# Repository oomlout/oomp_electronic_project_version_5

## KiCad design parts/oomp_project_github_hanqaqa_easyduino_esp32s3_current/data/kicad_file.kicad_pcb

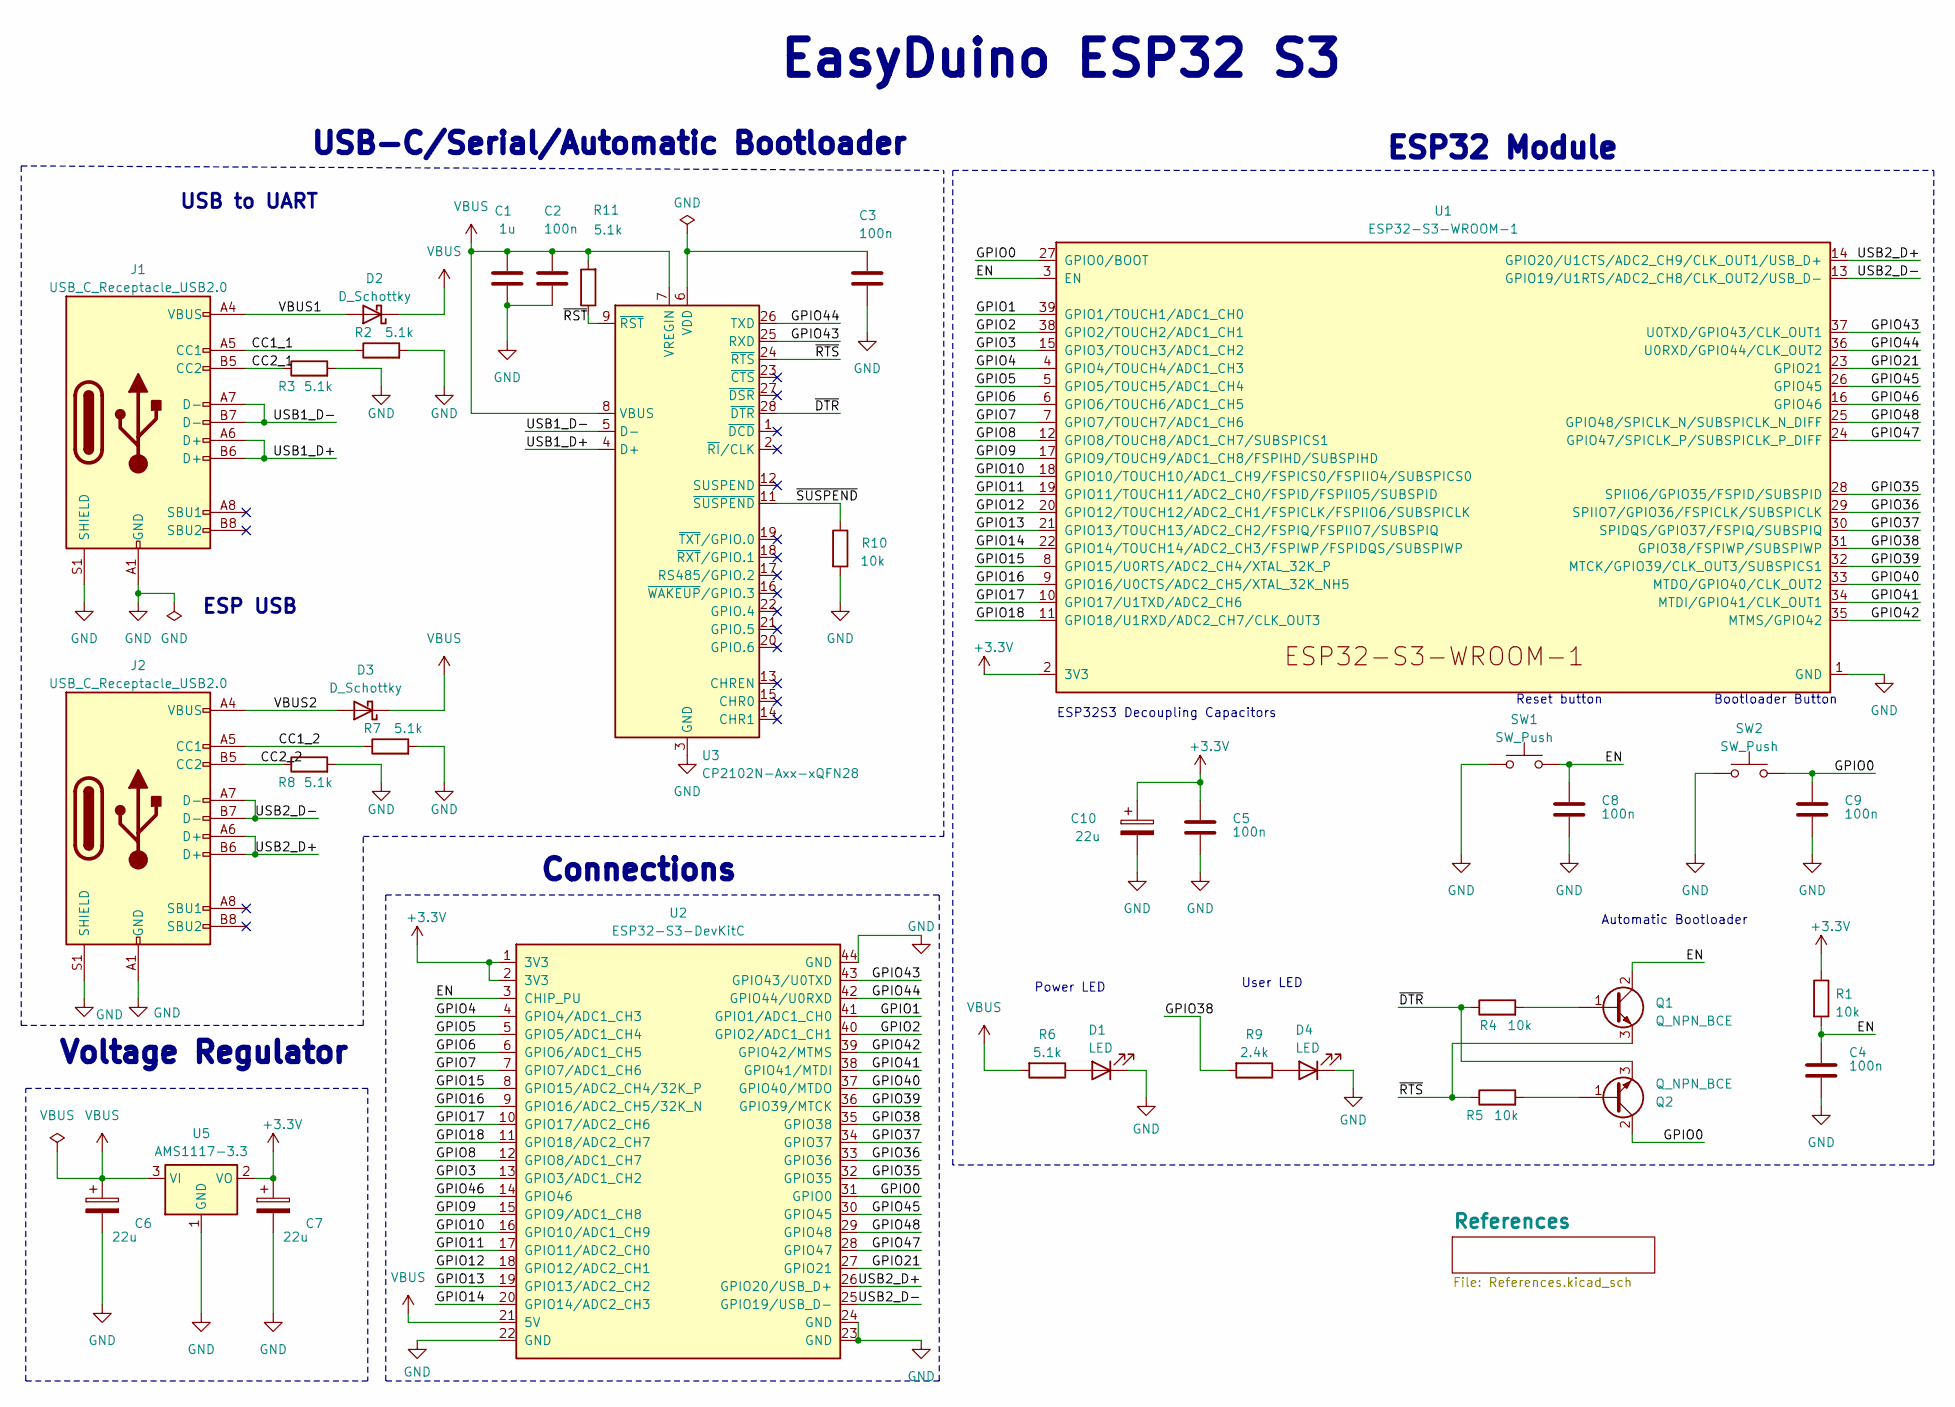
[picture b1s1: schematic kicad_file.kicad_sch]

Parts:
C1: 1u; C_0402_1005Metric; LCSC C52923
C2, C3, C4, C5, C8, C9: 100n; C_0402_1005Metric; LCSC C1525
C6, C7, C10: 22u; CP_EIA-3216-10_Kemet-I; LCSC C11366
D1, D4: LED; LED_0402_1005Metric; LCSC C434447
D2, D3: D_Schottky; D_0402_1005Metric; LCSC C2837790
J1, J2: USB_C_Receptacle_USB2.0; USB_C_Receptacle_G-Switch_GT-USB-7010ASV; LCSC C2765186
Q1, Q2: Q_NPN_BCE; SOT-23W; LCSC C916392
R1, R4, R5, R10: 10k; R_0402_1005Metric; LCSC C25744
R2, R3, R6, R7, R8, R11: 5.1k; R_0402_1005Metric; LCSC C25905
R9: 2.4k; R_0402_1005Metric; LCSC C25882
SW1, SW2: SW_Push; SW_Push_SPST_NO_Alps_SKRK; LCSC C720477
U1: ESP32-S3-WROOM-1; LCSC C2913197
U2: ESP32-S3-DevKitC
U3: CP2102N-Axx-xQFN28; QFN-28-1EP_5x5mm_P0.5mm_EP3.35x3.35mm; LCSC C6568
U5: AMS1117-3.3; SOT-223-3_TabPin2; LCSC C6186

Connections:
+3.3V: C5.1, C7.1, C10.1, R1.1, U1.2 (3V3), U2.1 (3V3), U2.2 (3V3), U5.2 (VO)
/CC1_1: J1.A5 (CC1), R2.1
/CC1_2: J2.A5 (CC1), R7.1
/CC2_1: J1.B5 (CC2), R3.1
/CC2_2: J2.B5 (CC2), R8.1
/EN: C4.1, C8.1, Q1.2 (C), R1.2, SW1.2, U1.3 (EN), U2.3 (CHIP_PU)
/GPIO0: C9.1, Q2.2 (C), SW2.2, U1.27 (GPIO0/BOOT), U2.31 (GPIO0)
/GPIO1: U1.39 (GPIO1/TOUCH1/ADC1_CH0), U2.41 (GPIO1/ADC1_CH0)
/GPIO2: U1.38 (GPIO2/TOUCH2/ADC1_CH1), U2.40 (GPIO2/ADC1_CH1)
/GPIO3: U1.15 (GPIO3/TOUCH3/ADC1_CH2), U2.13 (GPIO3/ADC1_CH2)
/GPIO4: U1.4 (GPIO4/TOUCH4/ADC1_CH3), U2.4 (GPIO4/ADC1_CH3)
/GPIO5: U1.5 (GPIO5/TOUCH5/ADC1_CH4), U2.5 (GPIO5/ADC1_CH4)
/GPIO6: U1.6 (GPIO6/TOUCH6/ADC1_CH5), U2.6 (GPIO6/ADC1_CH5)
/GPIO7: U1.7 (GPIO7/TOUCH7/ADC1_CH6), U2.7 (GPIO7/ADC1_CH6)
/GPIO8: U1.12 (GPIO8/TOUCH8/ADC1_CH7/SUBSPICS1), U2.12 (GPIO8/ADC1_CH7)
/GPIO9: U1.17 (GPIO9/TOUCH9/ADC1_CH8/FSPIHD/SUBSPIHD), U2.15 (GPIO9/ADC1_CH8)
/GPIO10: U1.18 (GPIO10/TOUCH10/ADC1_CH9/FSPICS0/FSPIIO4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), U2.16 (GPIO10/ADC1_CH9)
/GPIO11: U1.19 (GPIO11/TOUCH11/ADC2_CH0/FSPID/FSPIIO5/S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), U2.17 (GPIO11/ADC2_CH0)
/GPIO12: U1.20 (GPIO12/TOUCH12/ADC2_CH1/FSPICLK/FSPIIO6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), U2.18 (GPIO12/ADC2_CH1)
/GPIO13: U1.21 (GPIO13/TOUCH13/ADC2_CH2/FSPIQ/FSPIIO7/S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), U2.19 (GPIO13/ADC2_CH2)
/GPIO14: U1.22 (GPIO14/TOUCH14/ADC2_CH3/FSPIWP/FSPIDQS/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), U2.20 (GPIO14/ADC2_CH3)
/GPIO15: U1.8 (GPIO15/U0RTS/ADC2_CH4/XTAL_32K_P), U2.8 (GPIO15/ADC2_CH4/32K_P)
/GPIO16: U1.9 (GPIO16/U0CTS/ADC2_CH5/XTAL_32K_NH5), U2.9 (GPIO16/ADC2_CH5/32K_N)
/GPIO17: U1.10 (GPIO17/U1TXD/ADC2_CH6), U2.10 (GPIO17/ADC2_CH6)
/GPIO18: U1.11 (GPIO18/U1RXD/ADC2_CH7/CLK_OUT3), U2.11 (GPIO18/ADC2_CH7)
/GPIO21: U1.23 (GPIO21), U2.27 (GPIO21)
/GPIO35: U1.28 (SPIIO6/GPIO35/FSPID/SUBSPID), U2.32 (GPIO35)
/GPIO36: U1.29 (SPIIO7/GPIO36/FSPICLK/SUBSPICLK), U2.33 (GPIO36)
/GPIO37: U1.30 (SPIDQS/GPIO37/FSPIQ/SUBSPIQ), U2.34 (GPIO37)
/GPIO38: R9.2, U1.31 (GPIO38/FSPIWP/SUBSPIWP), U2.35 (GPIO38)
/GPIO39: U1.32 (MTCK/GPIO39/CLK_OUT3/SUBSPICS1), U2.36 (GPIO39/MTCK)
/GPIO40: U1.33 (MTDO/GPIO40/CLK_OUT2), U2.37 (GPIO40/MTDO)
/GPIO41: U1.34 (MTDI/GPIO41/CLK_OUT1), U2.38 (GPIO41/MTDI)
/GPIO42: U1.35 (MTMS/GPIO42), U2.39 (GPIO42/MTMS)
/GPIO43: U1.37 (U0TXD/GPIO43/CLK_OUT1), U2.43 (GPIO43/U0TXD), U3.25 (RXD)
/GPIO44: U1.36 (U0RXD/GPIO44/CLK_OUT2), U2.42 (GPIO44/U0RXD), U3.26 (TXD)
/GPIO45: U1.26 (GPIO45), U2.30 (GPIO45)
/GPIO46: U1.16 (GPIO46), U2.14 (GPIO46)
/GPIO47: U1.24 (GPIO47/SPICLK_P/SUBSPICLK_P_DIFF), U2.28 (GPIO47)
/GPIO48: U1.25 (GPIO48/SPICLK_N/SUBSPICLK_N_DIFF), U2.29 (GPIO48)
/USB1_D+: J1.A6 (D+), J1.B6 (D+), U3.4 (D+)
/USB1_D-: J1.A7 (D-), J1.B7 (D-), U3.5 (D-)
/USB2_D+: J2.A6 (D+), J2.B6 (D+), U1.14 (GPIO20/U1CTS/ADC2_CH9/CLK_OUT1/USB_D+), U2.26 (GPIO20/USB_D+)
/USB2_D-: J2.A7 (D-), J2.B7 (D-), U1.13 (GPIO19/U1RTS/ADC2_CH8/CLK_OUT2/USB_D-), U2.25 (GPIO19/USB_D-)
/VBUS1: D2.2 (A), J1.A4 (VBUS), J1.A9 (VBUS), J1.B4 (VBUS), J1.B9 (VBUS)
/VBUS2: D3.2 (A), J2.A4 (VBUS), J2.A9 (VBUS), J2.B4 (VBUS), J2.B9 (VBUS)
/~DTR: Q2.3 (E), R4.1, U3.28 (~DTR)
/~RST: R11.1, U3.9 (~RST)
/~RTS: Q1.3 (E), R5.1, U3.24 (~RTS)
/~SUSPEND: R10.1, U3.11 (~SUSPEND)
GND: C1.2, C2.2, C3.2, C4.2, C5.2, C6.2, C7.2, C8.2, C9.2, C10.2, D1.1 (K), D4.1 (K), J1.A1 (GND), J1.A12 (GND), J1.B1 (GND), J1.B12 (GND), J1.S1 (SHIELD), J2.A1 (GND), J2.A12 (GND), J2.B1 (GND), J2.B12 (GND), J2.S1 (SHIELD), R2.2, R3.2, R7.2, R8.2, R10.2, SW1.1, SW2.1, U1.1 (GND), U1.40 (GND), U1.41 (GND), U2.22 (GND), U2.23 (GND), U2.24 (GND), U2.44 (GND), U3.3 (GND), U3.29 (GND), U5.1 (GND)
unnamed: D1.2 (A), R6.1
unnamed: D4.2 (A), R9.1
unnamed: Q1.1 (B), R4.2
unnamed: Q2.1 (B), R5.2
unnamed: C3.1, U3.6 (VDD)
VBUS: C1.1, C2.1, C6.1, D2.1 (K), D3.1 (K), R6.2, R11.2, U2.21 (5V), U3.7 (VREGIN), U3.8 (VBUS), U5.3 (VI)

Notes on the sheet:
Automatic Bootloader
ESP USB
Power LED
ESP32 Module
User LED
USB-C/Serial/Automatic Bootloader
ESP32S3 Decoupling Capacitors
Connections
USB to UART
Voltage Regulator
Bootloader Button
EasyDuino ESP32 S3
Reset button

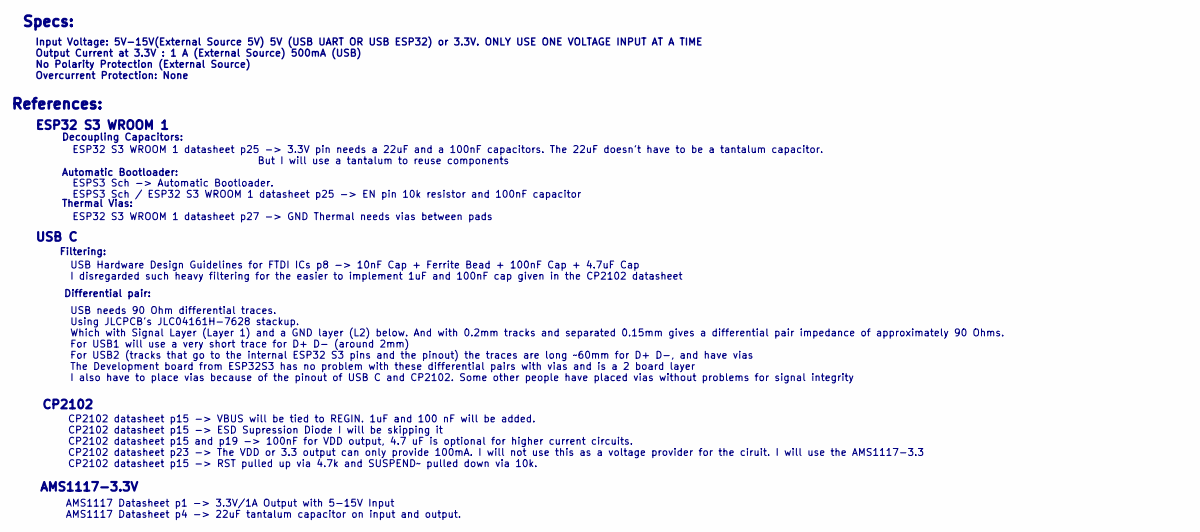
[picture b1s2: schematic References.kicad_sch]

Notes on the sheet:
Filtering:
Input Voltage: 5V-15V(External Source 5V) 5V (USB UART OR USB ESP32) or 3.3V. ONLY USE ONE VOLTAGE INPUT AT A TIME Output Current at 3.3V : 1 A (External Source) 500mA (USB) No Polarity Protection (External Source) Overcurrent Protection: None
Thermal Vias:
References:
ESP32 S3 WROOM 1
ESP32 S3 WROOM 1 datasheet p25 -> 3.3V pin needs a 22uF and a 100nF capacitors. The 22uF doesn't have to be a tantalum capacitor. But I will use a tantalum to reuse components ESPS3 Sch -> Automatic Bootloader. ESPS3 Sch / ESP32 S3 WROOM 1 datasheet p25 -> EN pin 10k resistor and 100nF capacitor ES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
Specs:
USB C
AMS1117-3.3V
CP2102 datasheet p15 -> VBUS will be tied to REGIN. 1uF and 100 nF will be added. CP2102 datasheet p15 -> ESD Supression Diode I will be skipping it CP2102 datasheet p15 and p19 -> 100nF for VDD output, 4.7 uF is optional for higher current circuits. CP2102 datasheet p23 -> The VDD or 3.3 output ca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
AMS1117 Datasheet p1 -> 3.3V/1A Output with 5-15V Input AMS1117 Datasheet p4 -> 22uF tantalum capacitor on input and output.
CP2102
Decoupling Capacitors:
USB needs 90 Ohm differential traces. Using JLCPCB's JLC04161H-7628 stackup. Which with Signal Layer (Layer 1) and a GND layer (L2) below. And with 0.2mm tracks and separated 0.15mm gives a differential pair impedance of approximately 90 Ohms. For USB1 will use a very short trace for D+ D- (around 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
Automatic Bootloader:
USB Hardware Design Guidelines for FTDI ICs p8 -> 10nF Cap + Ferrite Bead + 100nF Cap + 4.7uF Cap I disregarded such heavy filtering for the easier to implement 1uF and 100nF cap given in the CP2102 datasheet
Differential pair:

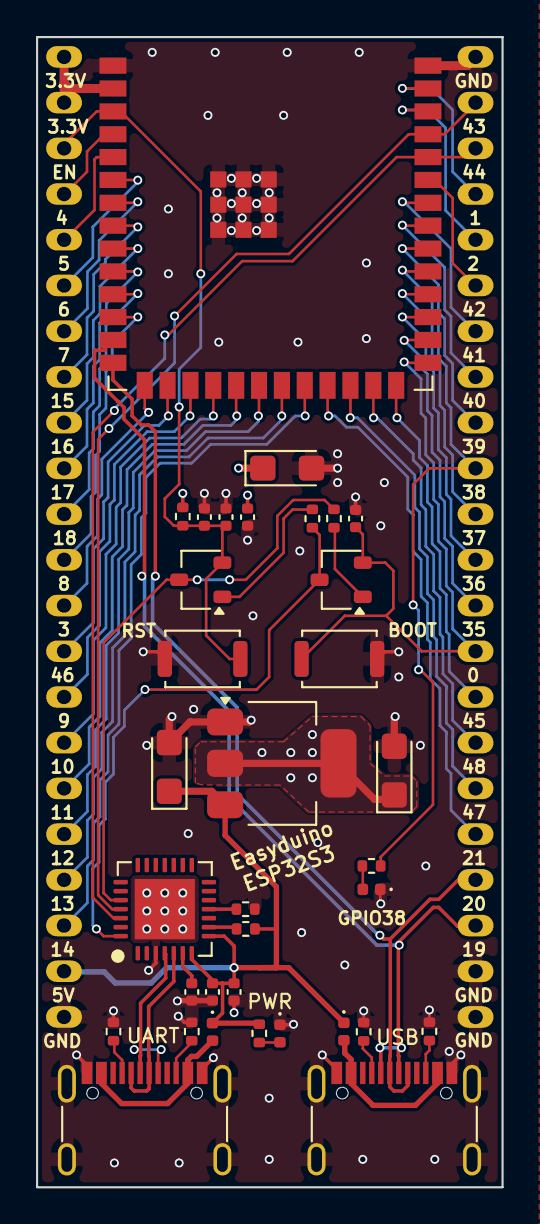
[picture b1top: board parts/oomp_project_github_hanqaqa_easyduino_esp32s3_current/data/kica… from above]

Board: 4 copper layers, 25.9 x 63.9 mm, 35 parts (0 on the bottom side), 57 nets.

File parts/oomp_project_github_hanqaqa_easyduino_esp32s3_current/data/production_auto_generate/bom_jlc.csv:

Comment,Designator,Footprint,LCSC Part #
100n,"C2,C3,C4,C5,C8,C9",Capacitor_SMD:C_0402_1005Metric,C1525
10k,"R1,R4,R5,R10",Resistor_SMD:R_0402_1005Metric,C25744
1u,C1,Capacitor_SMD:C_0402_1005Metric,C52923
2.4k,R9,Resistor_SMD:R_0402_1005Metric,C25882
22u,"C6,C7,C10",Capacitor_Tantalum_SMD:CP_EIA-3216-10_Kemet-I,C11366
5.1k,"R2,R3,R6,R7,R8,R11",Resistor_SMD:R_0402_1005Metric,C25905
AMS1117-3.3,U5,Package_TO_SOT_SMD:SOT-223-3_TabPin2,C6186
CP2102N-Axx-xQFN28,U3,Package_DFN_QFN:QFN-28-1EP_5x5mm_P0.5mm_EP3.35x3.35mm,C6568
D_Schottky,"D2,D3",Diode_SMD:D_0402_1005Metric,C2837790
ESP32-S3-DevKitC,U2,Espressif:ESP32-S3-DevKitC,-
ESP32-S3-WROOM-1,U1,Espressif:ESP32-S3-WROOM-1,C2913197
LED,"D1,D4",LED_SMD:LED_0402_1005Metric,C434447
Q_NPN_BCE,"Q1,Q2",Package_TO_SOT_SMD:SOT-23W,C916392
SW_Push,"SW1,SW2",Button_Switch_SMD:SW_Push_SPST_NO_Alps_SKRK,C720477
USB_C_Receptacle_USB2.0,"J1,J2",Connector_USB:USB_C_Receptacle_G-Switch_GT-USB-7010ASV,C2765186

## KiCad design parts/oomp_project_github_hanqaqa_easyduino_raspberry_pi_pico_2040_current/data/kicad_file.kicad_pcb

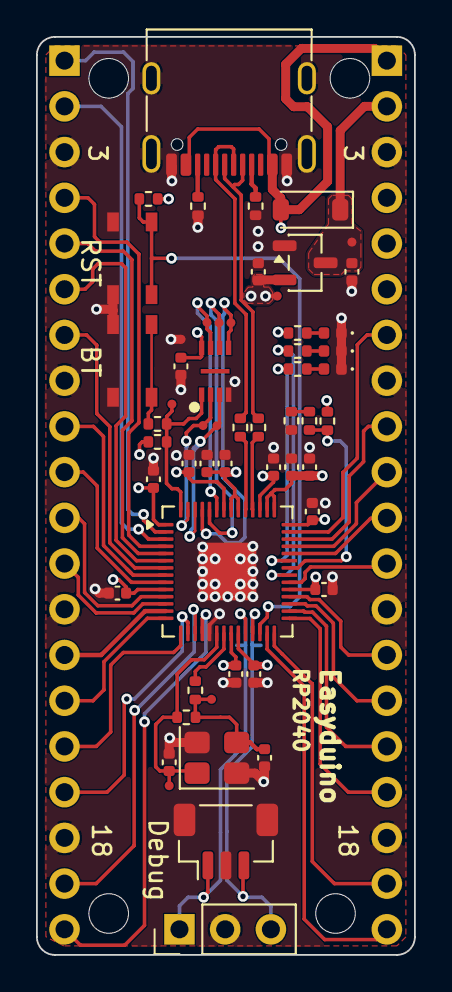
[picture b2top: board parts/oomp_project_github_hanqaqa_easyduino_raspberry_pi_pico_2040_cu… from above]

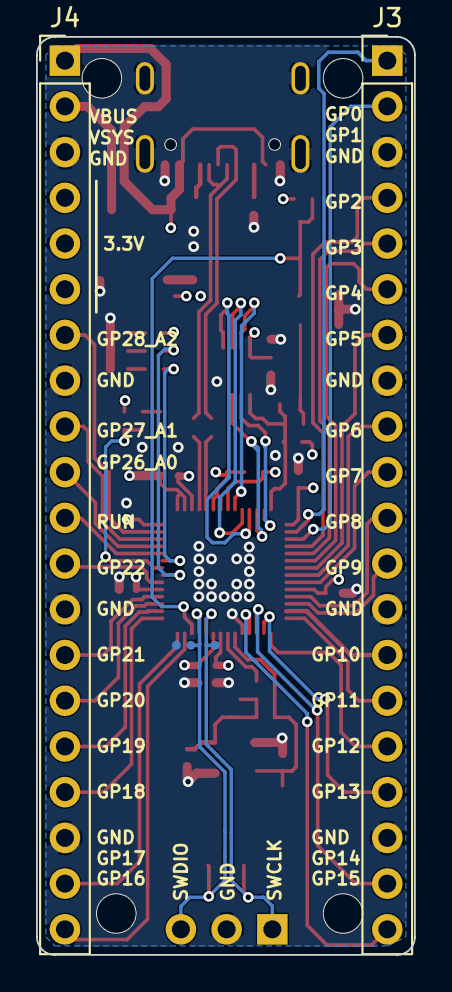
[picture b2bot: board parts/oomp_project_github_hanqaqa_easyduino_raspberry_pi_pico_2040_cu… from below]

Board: 4 copper layers, 21.0 x 51.0 mm, 65 parts (5 on the bottom side), 58 nets.

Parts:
C1, C2, C5, C6, C7, C8, C9, C10, C11, C12, C15: 100nF; C_0402_1005Metric
C3, C4, C13, C14: 1uF; C_0402_1005Metric
C16, C17: 27p; C_0402_1005Metric
D1: D_Schottky; D_SOD-123
D2, D3, D4: LED; LED_0402_1005Metric
H1, H2, H3, H4: MountingHole; MountingHole_2.2mm_M2
J1: USB_C_Receptacle_USB2.0; USB_C_Receptacle_G-Switch_GT-USB-7010ASV
J3, J4: Conn_01x20; PinHeader_1x20_P2.54mm_Vertical
J5: Conn_01x03; PinHeader_1x03_P2.54mm_Vertical
J6: Conn_01x03_MountingPin; JST_SH_BM03B-SRSS-TB_1x03-1MP_P1.00mm_Vertical
R1, R2, R3, R6, R7: 5.1k; R_0402_1005Metric
R4, R5: 27R; R_0402_1005Metric
R8, R9, R10, R11, R12, R13, R14, R15: 1k; R_0402_1005Metric
SW1, SW2: SW_Push; ALPSALPINE_SKRPACE010
TP1, TP2, TP3, TP4, TP5, TP6, TP7, TP8, TP9, TP10, TP11, TP12, TP13, TP14: TestPoint_pad
U1: XC6206P332MR; SOT-23-3
U2: RP2040; QFN-56-1EP_7x7mm_P0.4mm_EP3.2x3.2mm
U3: W25Q16JVUXIQ
Y1: 12MHz; Crystal_SMD_3225-4Pin_3.2x2.5mm

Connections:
+1V1: C1.1, C2.1, C3.1, U2.23 (DVDD), U2.45 (VREG_VOUT), U2.50 (DVDD)
+3.3V: C4.1, C5.1, C6.1, C7.1, C8.1, C9.1, C10.1, C11.1, C12.1, C14.1, C15.1, J4.4, J4.5, J4.6, R10.1, R11.1, R12.1, TP2.1 (1_1), U1.2 (VO), U2.1 (IOVDD), U2.10 (IOVDD), U2.22 (IOVDD), U2.33 (IOVDD), U2.42 (IOVDD), U2.43 (ADC_AVDD), U2.44 (VREG_IN), U2.48 (USB_VDD), U2.49 (IOVDD), U3.8 (VCC)
/CC1: J1.A5 (CC1), R1.1
/CC2: J1.B5 (CC2), R2.1
/GPIO0: J3.1, U2.2 (GPIO0)
/GPIO1: J3.2, U2.3 (GPIO1)
/GPIO2: J3.4, U2.4 (GPIO2)
/GPIO3: J3.5, U2.5 (GPIO3)
/GPIO4: J3.6, U2.6 (GPIO4)
/GPIO5: J3.7, U2.7 (GPIO5)
/GPIO6: J3.9, U2.8 (GPIO6)
/GPIO7: J3.10, U2.9 (GPIO7)
/GPIO8: J3.11, U2.11 (GPIO8)
/GPIO9: J3.12, U2.12 (GPIO9)
/GPIO10: J3.14, U2.13 (GPIO10)
/GPIO11: J3.15, U2.14 (GPIO11)
/GPIO12: J3.16, U2.15 (GPIO12)
/GPIO13: J3.17, U2.16 (GPIO13)
/GPIO14: J3.19, U2.17 (GPIO14)
/GPIO15: J3.20, U2.18 (GPIO15)
/GPIO16: J4.20, U2.27 (GPIO16)
/GPIO17: J4.19, U2.28 (GPIO17)
/GPIO18: J4.17, U2.29 (GPIO18)
/GPIO19: J4.16, U2.30 (GPIO19)
/GPIO20: J4.15, U2.31 (GPIO20)
/GPIO21: J4.14, U2.32 (GPIO21)
/GPIO22: J4.12, U2.34 (GPIO22)
/GPIO23: R13.1, U2.35 (GPIO23)
/GPIO24: R3.1, R6.2, U2.36 (GPIO24)
/GPIO25: R14.1, U2.37 (GPIO25)
/GPIO26_ADC0: J4.11, U2.38 (GPIO26_ADC0)
/GPIO27_ADC1: J4.10, U2.39 (GPIO27_ADC1)
/GPIO28_ADC2: J4.9, U2.40 (GPIO28_ADC2)
/GPIO29_ADC3: J4.7, U2.41 (GPIO29_ADC3)
/LED_3V3: D2.2 (A), R12.2
/LED_BUILT_IN1: D4.2 (A), R14.2
/LED_BUILT_IN2: D3.2 (A), R13.2
/QSPI_SCLK: TP9.1 (1_1), U2.52 (QSPI_SCLK), U3.6 (CLK)
/QSPI_SD0: TP10.1 (1_1), U2.53 (QSPI_SD0), U3.5 (DI(IO0))
/QSPI_SD1: TP11.1 (1_1), U2.55 (QSPI_SD1), U3.2 (DO(IO1))
/QSPI_SD2: TP12.1 (1_1), U2.54 (QSPI_SD2), U3.3 (IO2)
/QSPI_SD3: TP13.1 (1_1), U2.51 (QSPI_SD3), U3.7 (IO3)
/QSPI_SS: R10.2, R15.1, TP8.1 (1_1), U2.56 (QSPI_SS), U3.1 (~CS)
/RDIV: R6.1, R7.2
/RUN: R11.2, SW2.2, U2.26 (RUN)
/SW1_{PULL-UP}: R15.2, SW1.2
/SWCLK: J5.1, J6.1, TP5.1 (1_1), U2.24 (SWCLK)
/SWD: J5.3, J6.3, TP6.1 (1_1), U2.25 (SWD)
/USB_DN: J1.A7 (D-), J1.B7 (D-), R5.1
/USB_DP: J1.A6 (D+), J1.B6 (D+), R4.1
/USB_R_DN: R5.2, U2.46 (USB_DM)
/USB_R_DP: R4.2, U2.47 (USB_DP)
/Xin: C16.1, R8.1, TP3.1 (1_1), U2.20 (XIN), Y1.1
/Xout: R9.2, U2.21 (XOUT)
/XoutR: C17.1, R8.2, R9.1, TP4.1 (1_1), Y1.3
GND: C1.2, C2.2, C3.2, C4.2, C5.2, C6.2, C7.2, C8.2, C9.2, C10.2, C11.2, C12.2, C13.2, C14.2, C15.2, C16.2, C17.2, D2.1 (K), D3.1 (K), D4.1 (K), J1.A1 (GND), J1.A12 (GND), J1.B1 (GND), J1.B12 (GND), J1.SH (SHIELD), J3.3, J3.8, J3.13, J3.18, J4.3, J4.8, J4.13, J4.18, J5.2, J6.2, J6.MP (MountPin), R1.2, R2.2, R7.1, SW1.1, SW2.1, TP7.1 (1_1), TP14.1 (1_1), U1.1 (GND), U2.19 (TESTEN), U2.57 (GND), U3.4 (GND), Y1.2 (G), Y1.4 (G)
VBUS: D1.2 (A), J1.A4 (VBUS), J1.A9 (VBUS), J1.B4 (VBUS), J1.B9 (VBUS), J4.1, R3.2
VCC: C13.1, D1.1 (K), J4.2, TP1.1 (1_1), U1.3 (VI)

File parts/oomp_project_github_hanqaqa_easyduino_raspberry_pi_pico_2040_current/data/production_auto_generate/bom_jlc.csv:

Comment,Designator,Footprint,LCSC Part #
100nF,"C1,C2,C5,C6,C7,C8,C9,C10,C11,C12,C15",Capacitor_SMD:C_0402_1005Metric,C1525
12MHz,Y1,Crystal:Crystal_SMD_3225-4Pin_3.2x2.5mm,C9002
1k,"R9,R12,R13,R14,R15",Resistor_SMD:R_0402_1005Metric,C11702
1uF,"C3,C4,C13,C14",Capacitor_SMD:C_0402_1005Metric,C52923
27p,"C16,C17",Capacitor_SMD:C_0402_1005Metric,C1557
27R,"R4,R5",Resistor_SMD:R_0402_1005Metric,C2909343
5.1k,"R1,R2,R3,R6,R7",Resistor_SMD:R_0402_1005Metric,C25905
Conn_01x03,J5,Connector_PinHeader_2.54mm:PinHeader_1x03_P2.54mm_Vertical,-
Conn_01x03_MountingPin,J6,Connector_JST:JST_SH_BM03B-SRSS-TB_1x03-1MP_P1.00mm_Vertical,C160389
Conn_01x20,"J3,J4",Connector_PinHeader_2.54mm:PinHeader_1x20_P2.54mm_Vertical,-
D_Schottky,D1,Diode_SMD:D_SOD-123,C8598
LED,"D2,D3,D4",LED_SMD:LED_0402_1005Metric,C434448
RP2040,U2,Package_DFN_QFN:QFN-56-1EP_7x7mm_P0.4mm_EP3.2x3.2mm,C2040
SW_Push,"SW1,SW2",RP2040:ALPSALPINE_SKRPACE010,C139797
USB_C_Receptacle_USB2.0,J1,Connector_USB:USB_C_Receptacle_G-Switch_GT-USB-7010ASV,C2765186
W25Q16JVUXIQ,U3,RP2040:W25Q16JVUXIQ,C2843335
XC6206P332MR,U1,Package_TO_SOT_SMD:SOT-23-3,C347376
~,"TP1,TP2,TP3,TP4,TP5,TP6,TP7,TP8,TP9,TP10,TP11,TP12,TP13,TP14",rp2040_lib:TestPoint_pad,

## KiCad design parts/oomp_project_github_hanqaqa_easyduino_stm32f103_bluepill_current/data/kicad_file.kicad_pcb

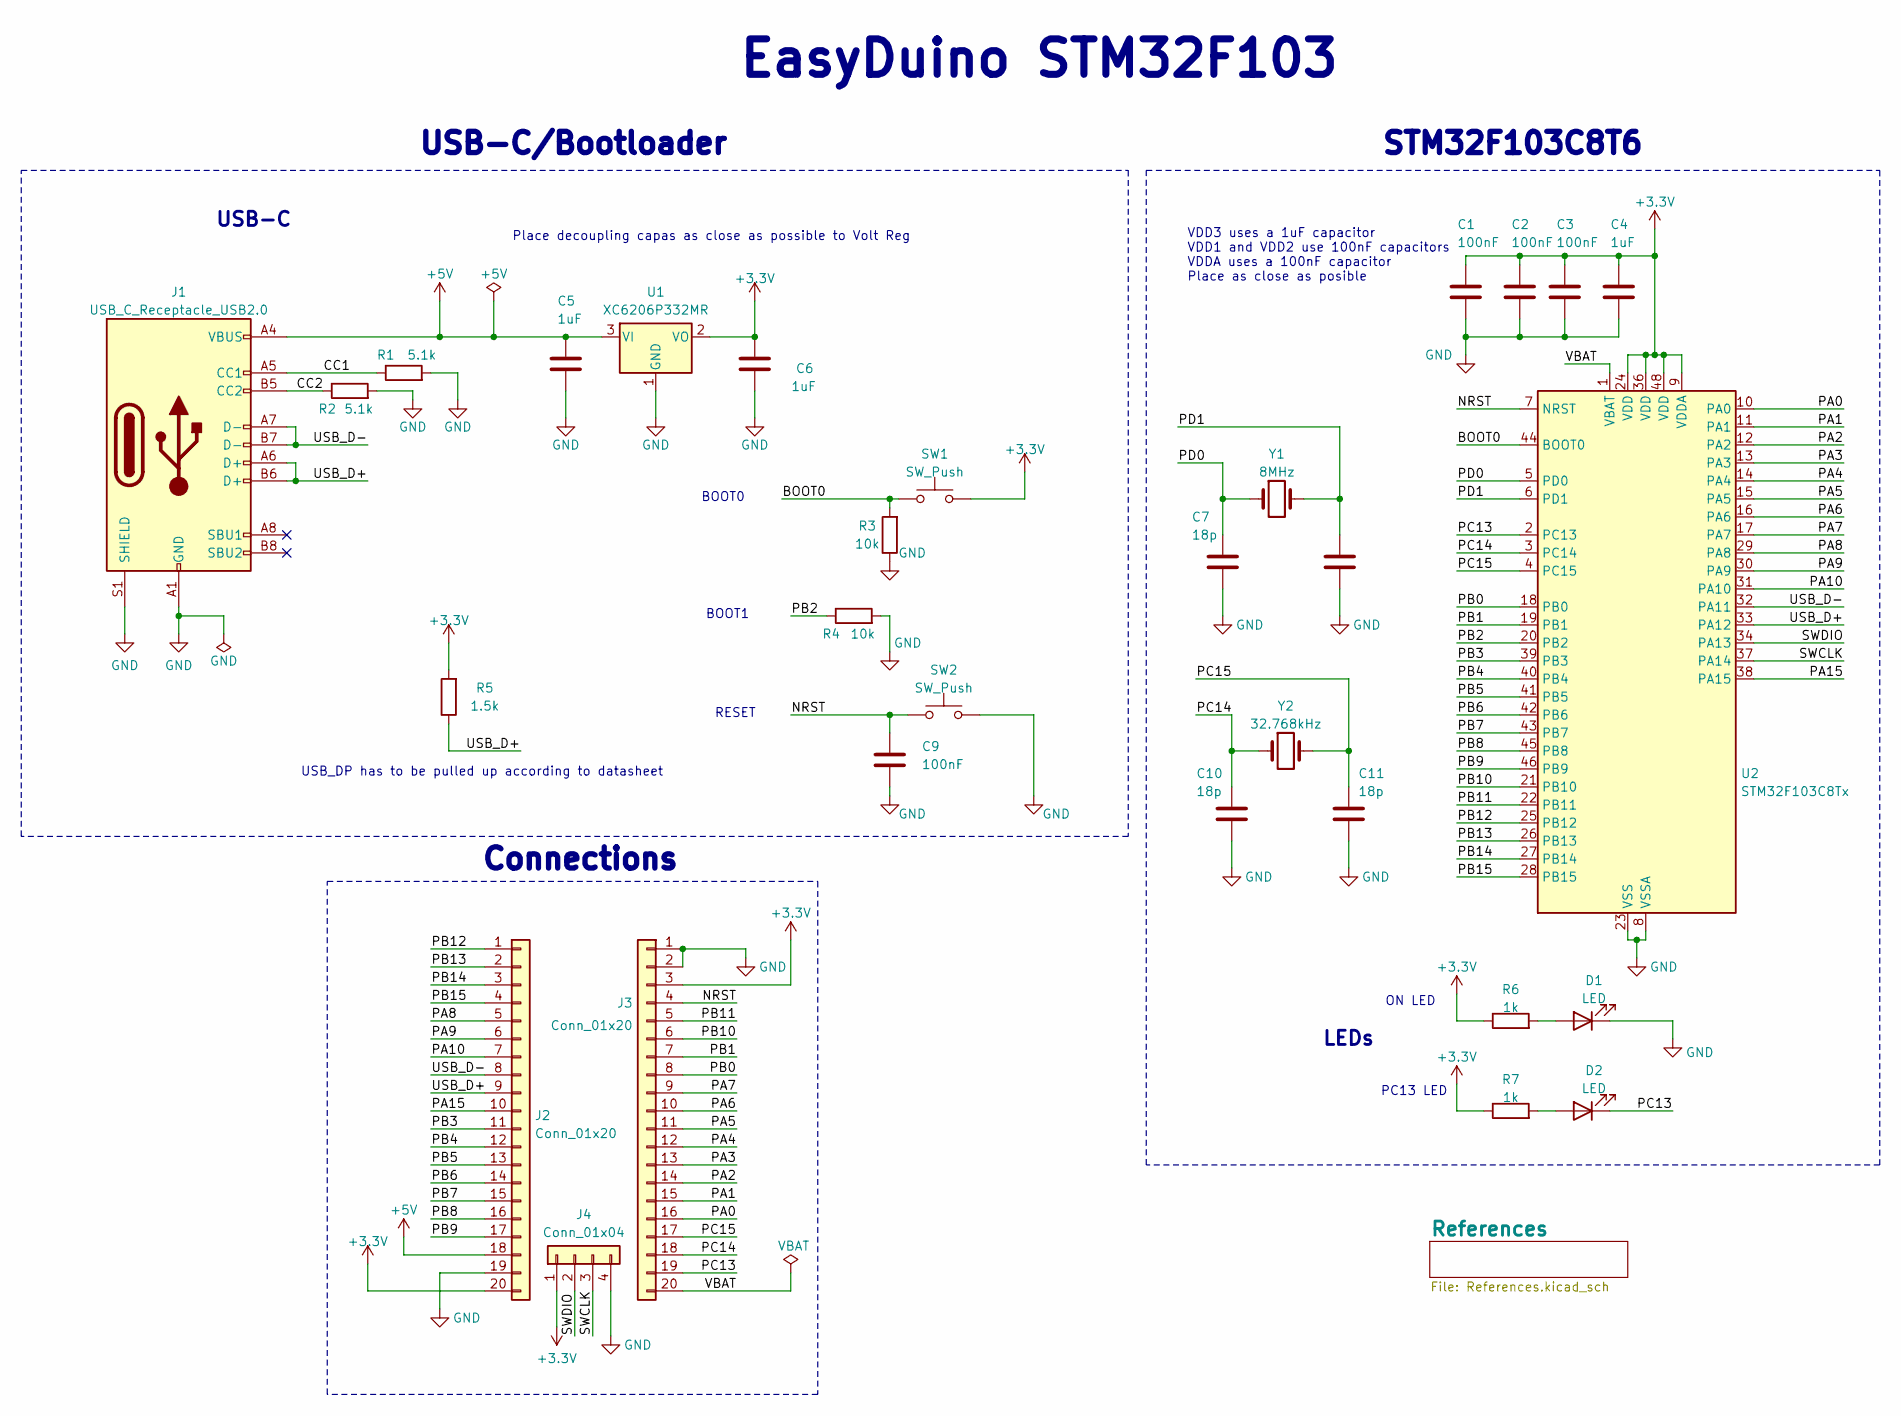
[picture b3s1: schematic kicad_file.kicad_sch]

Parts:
C1, C2, C3, C9: 100nF; C_0402_1005Metric; LCSC C1525
C4, C5, C6: 1uF; C_0402_1005Metric; LCSC C52923
C7, C8, C10, C11: 18p; C_0402_1005Metric; LCSC C1549
D1, D2: LED; LED_0402_1005Metric; LCSC C434448
J1: USB_C_Receptacle_USB2.0; USB_C_Receptacle_G-Switch_GT-USB-7010ASV; LCSC C2765186
J2, J3: Conn_01x20; PinHeader_1x20_P2.54mm_Vertical
J4: Conn_01x04; PinHeader_1x04_P2.54mm_Vertical
R1, R2: 5.1k; R_0402_1005Metric; LCSC C25905
R3, R4: 10k; R_0402_1005Metric; LCSC C25744
R5: 1.5k; R_0402_1005Metric; LCSC C25867
R6, R7: 1k; R_0402_1005Metric; LCSC C11702
SW1, SW2: SW_Push; ALPSALPINE_SKRPACE010; LCSC C139797
U1: XC6206P332MR; SOT-23-3; LCSC C347376
U2: STM32F103C8Tx; LQFP-48_7x7mm_P0.5mm; LCSC C8734
Y1: 8MHz; Crystal_SMD_5032-2Pin_5.0x3.2mm; LCSC C115962
Y2: 32.768kHz; Crystal_SMD_3215-2Pin_3.2x1.5mm; LCSC C32346

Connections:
+3.3V: C1.1, C2.1, C3.1, C4.1, C6.1, J2.20, J3.3, J4.1, R5.2, R6.1, R7.1, SW1.1, U1.2 (VO), U2.9 (VDDA), U2.24 (VDD), U2.36 (VDD), U2.48 (VDD)
+5V: C5.1, J1.A4 (VBUS), J1.A9 (VBUS), J1.B4 (VBUS), J1.B9 (VBUS), J2.18, U1.3 (VI)
/BOOT0: R3.2, SW1.2, U2.44 (BOOT0)
/CC1: J1.A5 (CC1), R1.1
/CC2: J1.B5 (CC2), R2.1
/NRST: C9.1, J3.4, SW2.2, U2.7 (NRST)
/PA0: J3.16, U2.10 (PA0)
/PA1: J3.15, U2.11 (PA1)
/PA2: J3.14, U2.12 (PA2)
/PA3: J3.13, U2.13 (PA3)
/PA4: J3.12, U2.14 (PA4)
/PA5: J3.11, U2.15 (PA5)
/PA6: J3.10, U2.16 (PA6)
/PA7: J3.9, U2.17 (PA7)
/PA8: J2.5, U2.29 (PA8)
/PA9: J2.6, U2.30 (PA9)
/PA10: J2.7, U2.31 (PA10)
/PA15: J2.10, U2.38 (PA15)
/PB0: J3.8, U2.18 (PB0)
/PB1: J3.7, U2.19 (PB1)
/PB2: R4.1, U2.20 (PB2)
/PB3: J2.11, U2.39 (PB3)
/PB4: J2.12, U2.40 (PB4)
/PB5: J2.13, U2.41 (PB5)
/PB6: J2.14, U2.42 (PB6)
/PB7: J2.15, U2.43 (PB7)
/PB8: J2.16, U2.45 (PB8)
/PB9: J2.17, U2.46 (PB9)
/PB10: J3.6, U2.21 (PB10)
/PB11: J3.5, U2.22 (PB11)
/PB12: J2.1, U2.25 (PB12)
/PB13: J2.2, U2.26 (PB13)
/PB14: J2.3, U2.27 (PB14)
/PB15: J2.4, U2.28 (PB15)
/PC13: D2.1 (K), J3.19, U2.2 (PC13)
/PC14: C10.1, J3.18, U2.3 (PC14), Y2.1
/PC15: C11.1, J3.17, U2.4 (PC15), Y2.2
/PD0: C7.1, U2.5 (PD0), Y1.1
/PD1: C8.1, U2.6 (PD1), Y1.2
/SWCLK: J4.3, U2.37 (PA14)
/SWDIO: J4.2, U2.34 (PA13)
/USB_D+: J1.A6 (D+), J1.B6 (D+), J2.9, R5.1, U2.33 (PA12)
/USB_D-: J1.A7 (D-), J1.B7 (D-), J2.8, U2.32 (PA11)
/VBAT: J3.20, U2.1 (VBAT)
GND: C1.2, C2.2, C3.2, C4.2, C5.2, C6.2, C7.2, C8.2, C9.2, C10.2, C11.2, D1.1 (K), J1.A1 (GND), J1.A12 (GND), J1.B1 (GND), J1.B12 (GND), J1.S1 (SHIELD), J2.19, J3.1, J3.2, J4.4, R1.2, R2.2, R3.1, R4.2, SW2.1, U1.1 (GND), U2.8 (VSSA), U2.23 (VSS), U2.35 (VSS), U2.47 (VSS)
unnamed: D1.2 (A), R6.2
unnamed: D2.2 (A), R7.2

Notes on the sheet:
STM32F103C8T6
BOOT0
ON LED
RESET
Place decoupling capas as close as possible to Volt Reg
BOOT1
PC13 LED
EasyDuino STM32F103
USB_DP has to be pulled up according to datasheet
VDD3 uses a 1uF capacitor VDD1 and VDD2 use 100nF capacitors VDDA uses a 100nF capacitor Place as close as posible
USB-C
USB-C/Bootloader
LEDs
Connections

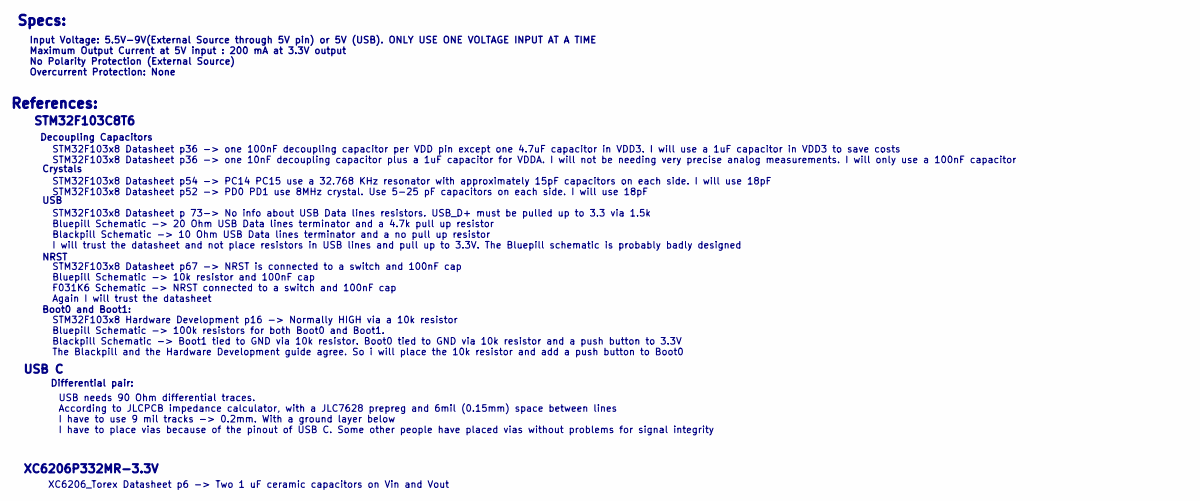
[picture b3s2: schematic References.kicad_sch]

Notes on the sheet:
USB C
Specs:
STM32F103x8 Datasheet p36 -> one 100nF decoupling capacitor per VDD pin except one 4.7uF capacitor in VDD3. I will use a 1uF capacitor in VDD3 to save costs STM32F103x8 Datasheet p36 -> one 10nF decoupling capacitor plus a 1uF capacitor for VDDA. I will not be needing very precise analog measuremen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
References:
USB
XC6206_Torex Datasheet p6 -> Two 1 uF ceramic capacitors on Vin and Vout
USB needs 90 Ohm differential traces. According to JLCPCB impedance calculator, with a JLC7628 prepreg and 6mil (0.15mm) space between lines I have to use 9 mil tracks -> 0.2mm. With a ground layer below I have to place vias because of the pinout of USB C. Some other people have placed vias without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
Input Voltage: 5.5V-9V(External Source through 5V pin) or 5V (USB). ONLY USE ONE VOLTAGE INPUT AT A TIME Maximum Output Current at 5V input : 200 mA at 3.3V output No Polarity Protection (External Source) Overcurrent Protection: None
Boot0 and Boot1:
XC6206P332MR-3.3V
Crystals
Decoupling Capacitors
NRST
STM32F103C8T6
Differential pair:

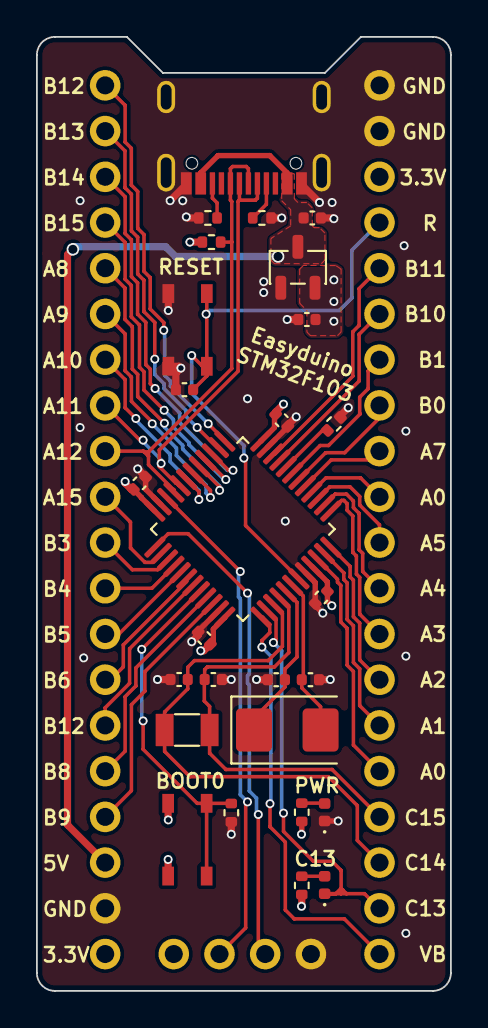
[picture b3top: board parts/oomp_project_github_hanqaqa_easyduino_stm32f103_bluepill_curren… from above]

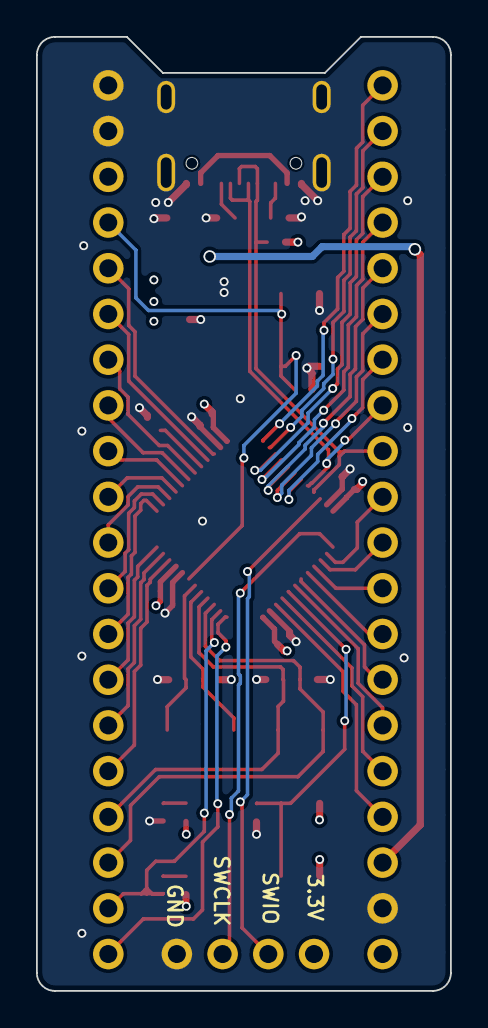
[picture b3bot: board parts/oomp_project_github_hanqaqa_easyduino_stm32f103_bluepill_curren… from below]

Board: 4 copper layers, 23.0 x 53.0 mm, 30 parts (2 on the bottom side), 47 nets.

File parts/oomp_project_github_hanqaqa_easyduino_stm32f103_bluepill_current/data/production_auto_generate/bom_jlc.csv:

Comment,Designator,Footprint,LCSC Part #
1.5k,R5,Resistor_SMD:R_0402_1005Metric,C25867
100nF,"C1,C2,C3,C9",Capacitor_SMD:C_0402_1005Metric,C1525
10k,"R3,R4",Resistor_SMD:R_0402_1005Metric,C25744
18p,"C7,C8,C10,C11",Capacitor_SMD:C_0402_1005Metric,C1549
1k,"R6,R7",Resistor_SMD:R_0402_1005Metric,C11702
1uF,"C4,C5,C6",Capacitor_SMD:C_0402_1005Metric,C52923
32.768kHz,Y2,Crystal:Crystal_SMD_3215-2Pin_3.2x1.5mm,C32346
5.1k,"R1,R2",Resistor_SMD:R_0402_1005Metric,C25905
8MHz,Y1,Crystal:Crystal_SMD_5032-2Pin_5.0x3.2mm,C115962
Conn_01x04,J4,Connector_PinHeader_2.54mm:PinHeader_1x04_P2.54mm_Vertical,-
Conn_01x20,"J2,J3",Connector_PinHeader_2.54mm:PinHeader_1x20_P2.54mm_Vertical,-
LED,"D1,D2",LED_SMD:LED_0402_1005Metric,C434448
STM32F103C8Tx,U2,Package_QFP:LQFP-48_7x7mm_P0.5mm,C8734
SW_Push,"SW1,SW2",Bluepill_Library:ALPSALPINE_SKRPACE010,C139797
USB_C_Receptacle_USB2.0,J1,Connector_USB:USB_C_Receptacle_G-Switch_GT-USB-7010ASV,C2765186
XC6206P332MR,U1,Package_TO_SOT_SMD:SOT-23-3,C347376

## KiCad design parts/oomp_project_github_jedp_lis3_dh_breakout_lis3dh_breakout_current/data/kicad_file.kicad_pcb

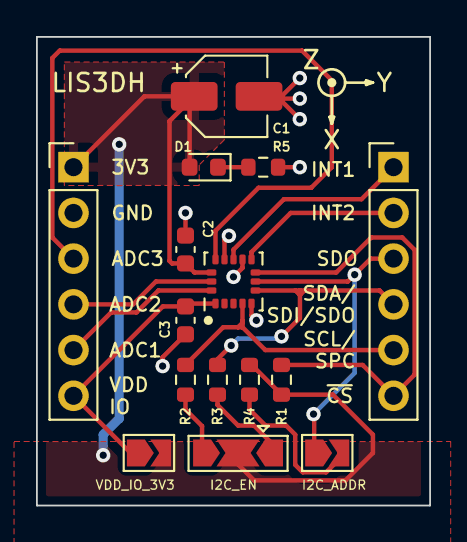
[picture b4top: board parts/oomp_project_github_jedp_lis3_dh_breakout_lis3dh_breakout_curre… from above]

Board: 2 copper layers, 21.8 x 26.0 mm, 15 parts (0 on the bottom side), 16 nets.

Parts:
C1: 10µ; CP_Elec_4x4.5
C2, C3: 0.1µ; C_0603_1608Metric
D1: LED PWR; LED_0603_1608Metric
I2C_ADDR: I2C ADDR; SolderJumper-2_P1.3mm_Open_TrianglePad1.0x1.5mm
I2C_EN: I2C EN; SolderJumper-3_P2.0mm_Open_TrianglePad1.0x1.5mm
J1, J2: Conn_01x06_Female; PinHeader_1x06_P2.54mm_Vertical
LIS3DH: LIS3DH; LGA-16_3x3mm_P0.5mm_LayoutBorder3x5y
R1, R4: 100k; R_0603_1608Metric
R2, R3: 10k; R_0603_1608Metric
R5: 1k; R_0603_1608Metric
VDD_IO_3V3: VCC_IO = VCC; SolderJumper-2_P1.3mm_Open_TrianglePad1.0x1.5mm

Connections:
+3V3: C1.1, C2.1, D1.2 (A), I2C_EN.2 (C), J2.1, LIS3DH.14 (VDD), R1.1, R4.1, VDD_IO_3V3.2 (B)
ADC1: J2.5, LIS3DH.16 (ADC1)
ADC2: J2.4, LIS3DH.15 (ADC2)
ADC3: J2.3, LIS3DH.13 (ADC3)
CS/MODE: J1.6, LIS3DH.8 (CS), R1.2
GND: C1.2, C2.2, C3.2, J2.2, LIS3DH.5 (GND), LIS3DH.10 (GND), LIS3DH.12 (GND), R5.1
INT1: J1.1, LIS3DH.11 (INT1)
INT2: J1.2, LIS3DH.9 (INT2)
unnamed: D1.1 (K), R5.2
unnamed: I2C_EN.1 (A), R3.1
unnamed: I2C_EN.3 (B), R2.1
unnamed: I2C_ADDR.2 (B), R4.2
SCL/SPC: J1.5, LIS3DH.4 (SCL/SPC), R2.2
SDA/SDI/SDO: J1.4, LIS3DH.6 (SDA/SDI/SDO), R3.2
SDO/SA0: I2C_ADDR.1 (A), J1.3, LIS3DH.7 (SDO/SA0)
VDD_IO: C3.1, J2.6, LIS3DH.1 (VDD_IO), VDD_IO_3V3.1 (A)
